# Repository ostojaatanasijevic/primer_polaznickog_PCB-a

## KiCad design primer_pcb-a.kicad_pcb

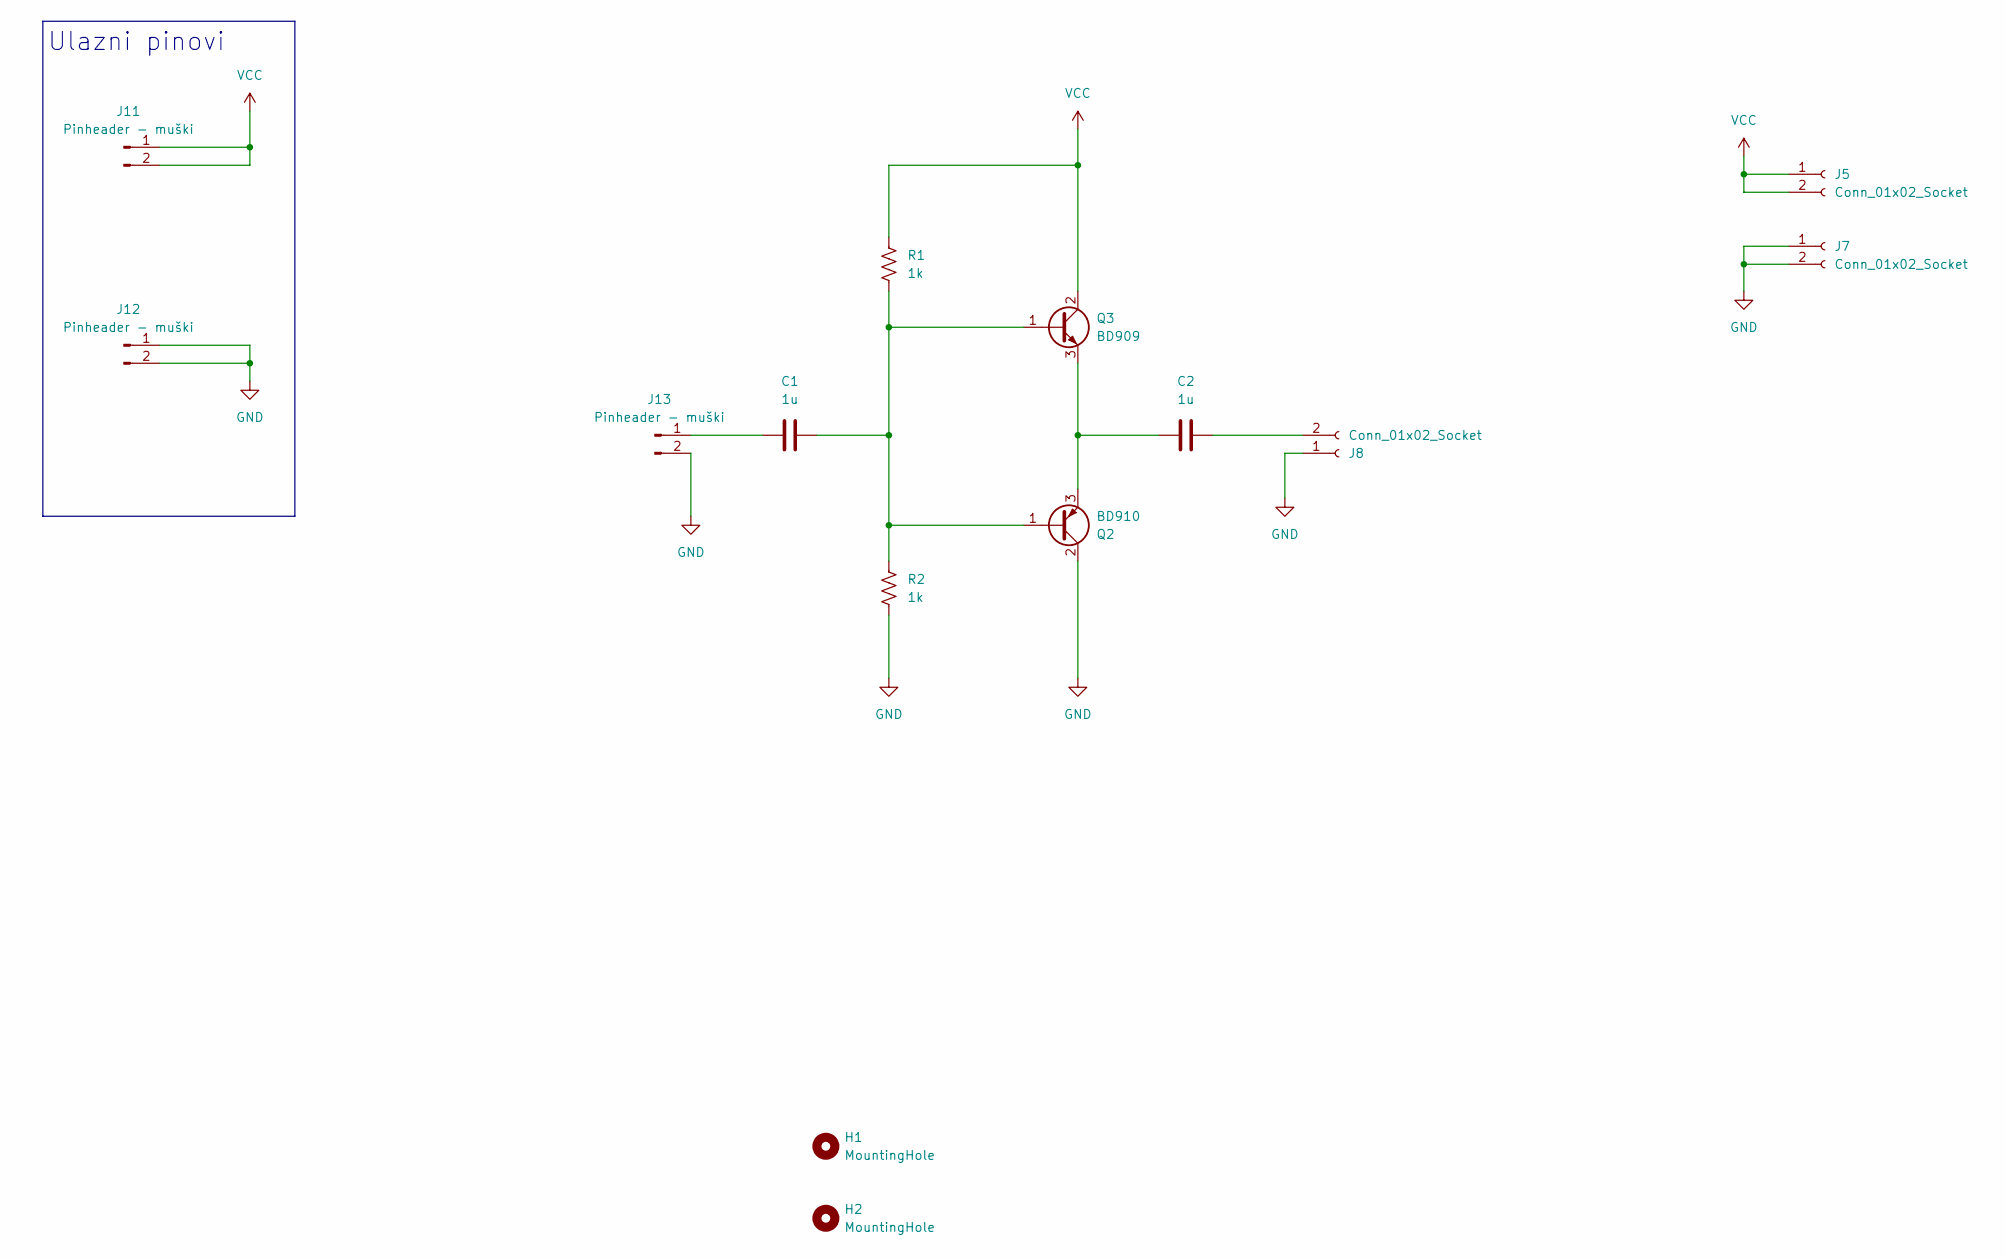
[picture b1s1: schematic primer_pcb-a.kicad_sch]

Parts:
C1, C2: 1u; C_1206_3216Metric_Pad1.33x1.80mm_HandSolder
H1, H2: MountingHole; MountingHole_3.2mm_M3
J5, J7, J8: Conn_01x02_Socket; PinSocket_1x02_P2.54mm_Polegnut
J11, J12, J13: Pinheader - muški; PinHeader_1x02_P2.54mm_Polegnut
Q2: BD910; TO-220-3_Vertical
Q3: BD909; TO-220-3_Vertical
R1, R2: 1k; R_1206_3216Metric_Pad1.30x1.75mm_HandSolder

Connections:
GND: J7.1, J7.2, J8.1, J12.1, J12.2, J13.2, Q2.2 (C), R2.2
unnamed: C2.2, J8.2
unnamed: C1.1, J13.1
unnamed: C1.2, Q2.1 (B), Q3.1 (B), R1.2, R2.1
unnamed: C2.1, Q2.3 (E), Q3.3 (E)
VCC: J5.1, J5.2, J11.1, J11.2, Q3.2 (C), R1.1

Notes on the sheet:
Ulazni pinovi

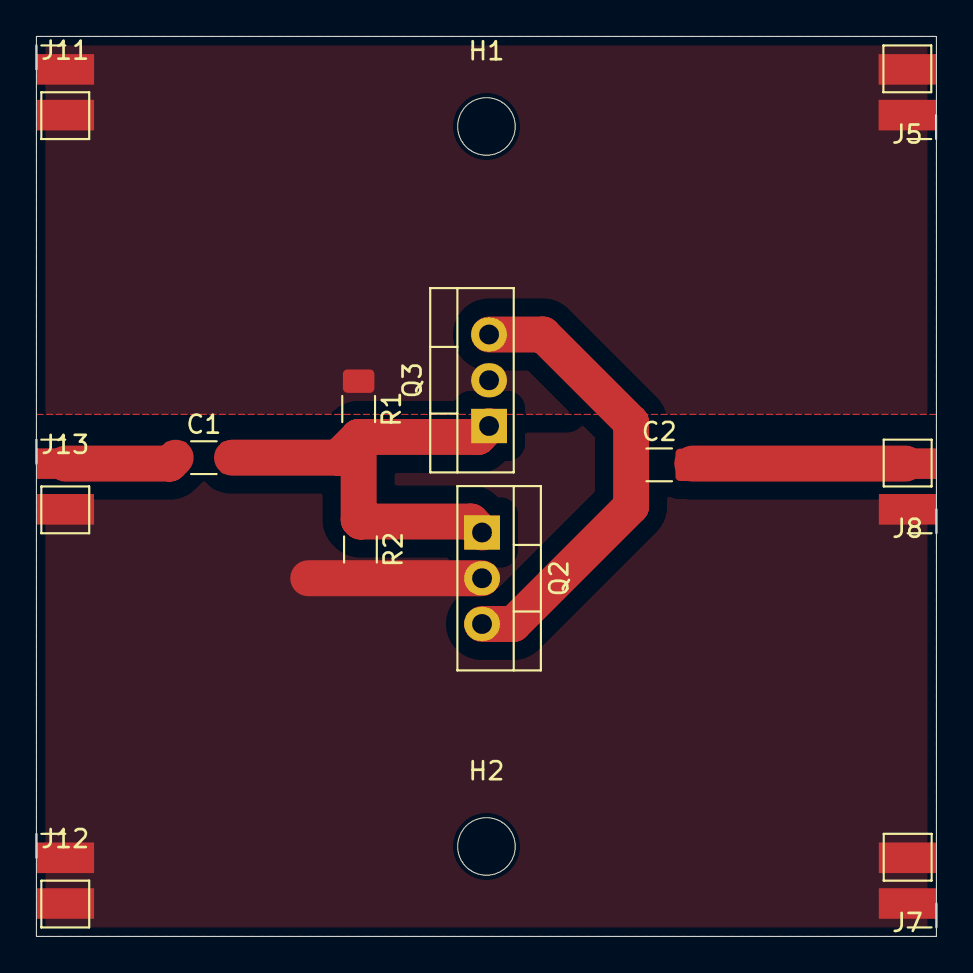
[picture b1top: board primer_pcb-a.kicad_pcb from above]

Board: 2 copper layers, 50.0 x 50.0 mm, 14 parts (0 on the bottom side), 6 nets.

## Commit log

2025-04-17 Init
2025-04-19 New footprints, new connectors.
2025-04-19 Readme
2025-04-19 Added mounting holes.
2025-04-19 Updated pins
